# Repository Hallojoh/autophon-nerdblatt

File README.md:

We try to get an flipboard display running on a new PCB

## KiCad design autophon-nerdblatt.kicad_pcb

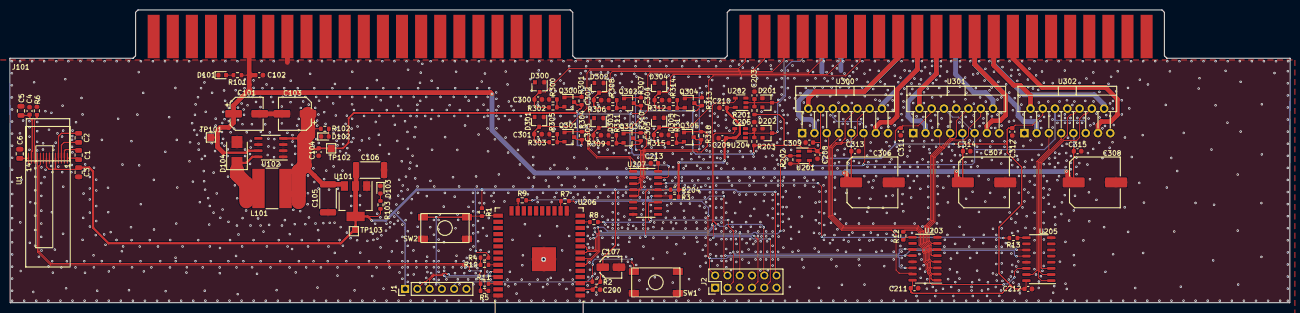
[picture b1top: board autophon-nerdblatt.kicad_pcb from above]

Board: 2 copper layers, 265.0 x 60.6 mm, 115 parts (0 on the bottom side), 82 nets.

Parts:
C1, C2, C3: 1u; C_0805_2012Metric
C4, C104, C200, C300, C301, C302, C303, C304, C305, C309, C311, C312: 100n; C_0603_1608Metric
C5, C6: 10u; C_0805_2012Metric
C101, C103: 120u; CP_Elec_6.3x7.7
C102, C313, C314, C315: 100n/25V; C_0603_1608Metric
C105, C106: 10u; C_2512_6332Metric
C107: 22u; C_Elec_4x5.8
C203, C205, C208, C209, C210: 1n; C_0603_1608Metric
C211, C212, C213: 10n; C_0603_1608Metric
C306, C307, C308: 470uF; C_Elec_10x10.2
D101, D102, D103: LED gn; LED_0603_1608Metric
D104: MBRS130; D_SMB
D201, D202, D300, D301, D302, D303, D304, D305: 5v6; D_SOT-23_ANK
J1: Conn_01x06_Female; PinHeader_1x06_P2.54mm_Vertical
J2: Conn_02x06_Odd_Even; PinHeader_2x06_P2.54mm_Vertical
J101: board-edge-connector; autophon-pcb-edge-connector
L101: 100uH; L_Bourns-SRN8040_8x8.15mm
Q300, Q301, Q302, Q303, Q304, Q305: BSS84; SOT-23
R1, R2, R3, R4, R5, R202, R204, R301, R302, R304, R305, R307, R308, R310, R311, R313, R314, R316, R317: 10k; R_0603_1608Metric
R6: 910k; R_0603_1608Metric
R7, R8, R9, R10, R11, R12, R13: 33R; R_0603_1608Metric
R101: 1k2; R_0603_1608Metric
R102: 200R; R_0603_1608Metric
R103: 100R; R_0603_1608Metric
R201, R203: 4k7; R_0603_1608Metric
R300, R303, R306, R309, R312, R315: 51R; R_0603_1608Metric
SW1, SW2: SW_Push; NAMAE_JTP-1138
TP101: 24V; TestPoint_Pad_1.5x1.5mm
TP102: 5V; TestPoint_Pad_1.5x1.5mm
TP103: VCC; TestPoint_Pad_1.5x1.5mm
U1: EA_W096016-XALW; EA W096016-XA
U101: LM1117-3.3; SOT-223-3_TabPin2
U102: LM2594M-5.0; SO-8_3.9x4.9mm_P1.27mm
U201, U202, U204: SN74LV1T34; SOT-23-5
U203, U205, U207: 74AHCT595; SO-16_3.9x9.9mm_P1.27mm
U206: ESP32-WROOM-32
U300, U301, U302: L298HN; TO-220-15_P2.54x2.54mm_StaggerOdd_Lead4.58mm_Vertical

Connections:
+5V: C103.1, C104.1, C105.1, C208.1, C211.1, C212.1, C213.1, C309.1, C311.1, C312.1, L101.2, Q300.3 (D), Q301.3 (D), Q302.3 (D), Q303.3 (D), Q304.3 (D), Q305.3 (D), R102.1, R201.1, R203.1, R301.1, R304.1, R307.1, R310.1, R313.1, R316.1, TP102.1, U101.3 (VI), U102.4 (FB), U201.5 (VCC), U203.16 (VCC), U205.16 (VCC), U207.16 (VCC), U300.4 (Vs), U301.4 (Vs), U302.4 (Vs)
+24V: C101.1, C102.1, C306.1, C307.1, C308.1, C313.1, C314.1, C315.1, J101.6A, J101.39B, R101.1, TP101.1, U102.7 (VIN), U300.9 (Vss), U301.9 (Vss), U302.9 (Vss)
/ESP32_Shiftregs/ESP32_EN: J1.5, R2.2, SW1.2, U206.3 (EN)
/ESP32_Shiftregs/ESP32_GPIO0: J1.4, R1.2, SW2.2, U206.25 (IO0)
/ESP32_Shiftregs/ESP32_RX: J1.2, U206.34 (RXD0/IO3)
/ESP32_Shiftregs/ESP32_TX: J1.3, U206.35 (TXD0/IO1)
/ESP32_Shiftregs/HALL_INDEX_3V: J2.9, U202.4 (Y), U206.7 (IO35)
/ESP32_Shiftregs/HALL_ROTOR_3V: J2.10, U204.4 (Y), U206.6 (IO34)
/ESP32_Shiftregs/I2C_SCL: R11.1, U206.36 (IO22)
/ESP32_Shiftregs/I2C_SDA: R10.1, U206.33 (IO21)
/ESP32_Shiftregs/MOT_EN_3V: J2.6, R202.1, U201.2 (A), U206.8 (IO32)
/ESP32_Shiftregs/SER_QH_2: R13.2, U207.14 (SER)
/ESP32_Shiftregs/SPI_CLK: R8.1, U206.13 (IO14)
/ESP32_Shiftregs/SPI_CLK-t: J2.3, R8.2, U203.11 (SRCLK), U205.11 (SRCLK), U207.11 (SRCLK)
/ESP32_Shiftregs/SPI_COPI: R7.1, U206.16 (IO13)
/ESP32_Shiftregs/SPI_COPI-t: J2.2, R7.2, U203.14 (SER)
/ESP32_Shiftregs/~HALL_EN_3V~: J2.7, R204.2, U206.9 (IO33), U207.13 (~OE)
/ESP32_Shiftregs/~SPI_CSO-t~: J2.4, R3.2, R9.2, U203.12 (RCLK), U205.12 (RCLK), U207.12 (RCLK)
/ESP32_Shiftregs/~SPI_CSO~: R9.1, U206.23 (IO15)
ABCDEF_HALL_GND: C3.2, C4.2, C5.2, C6.2, C101.2, C102.2, C103.2, C104.2, C105.2, C106.2, C107.2, C200.2, C203.2, C205.2, C208.2, C209.2, C210.2, C211.2, C212.2, C213.2, C300.2, C301.2, C302.2, C303.2, C304.2, C305.2, C306.2, C307.2, C308.2, C309.2, C311.2, C312.2, C313.2, C314.2, C315.2, D101.1 (K), D102.1 (K), D103.1 (K), D104.2 (A), D201.2 (A), D202.2 (A), D300.2 (A), D301.2 (A), D302.2 (A), D303.2 (A), D304.2 (A), D305.2 (A), J1.6, J2.1, J2.5, J2.8, J2.11, J101.8A, J101.17B, J101.18B, J101.37B, R6.1, R202.2, R302.2, R305.2, R308.2, R311.2, R314.2, R317.2, SW1.1, SW2.1, U1.7 (VSS), U101.1 (GND), U102.1 (NC), U102.2 (NC), U102.3 (NC), U102.6 (GND), U201.3 (GND), U202.3 (GND), U203.8 (GND), U203.13 (~OE), U204.3 (GND), U205.8 (GND), U205.13 (~OE), U206.1 (GND), U206.15 (GND), U206.38 (GND), U206.39 (GND), U207.8 (GND), U300.1 (SENSE_A), U300.8 (GND), U300.15 (SENSE_B), U301.1 (SENSE_A), U301.8 (GND), U301.15 (SENSE_B), U302.1 (SENSE_A), U302.8 (GND), U302.15 (SENSE_B)
ABCDEF_HALL_INDEX: C203.1, D201.1 (K), J101.20B, R201.2, U202.2 (A)
ABCDEF_HALL_ROTOR: C205.1, D202.1 (K), J101.19B, R203.2, U204.2 (A)
A_HALL_PWR: C300.1, D300.1 (K), J101.23A, R300.1
A_MOT_NEG: J101.14B, U300.3 (OUT2)
A_MOT_NEG_DRV: U203.1 (QB), U300.7 (IN2)
A_MOT_POS: J101.31A, U300.2 (OUT1)
A_MOT_POS_DRV: U203.15 (QA), U300.5 (IN1)
B_HALL_PWR: C301.1, D301.1 (K), J101.24A, R303.1
B_MOT_NEG: J101.13B, U300.14 (OUT4)
B_MOT_NEG_DRV: U203.3 (QD), U300.12 (IN4)
B_MOT_POS: J101.32A, U300.13 (OUT3)
B_MOT_POS_DRV: U203.2 (QC), U300.10 (IN3)
C_HALL_PWR: C302.1, D302.1 (K), J101.25A, R306.1
C_MOT_NEG: J101.12B, U301.3 (OUT2)
C_MOT_NEG_DRV: U203.5 (QF), U301.7 (IN2)
C_MOT_POS: J101.33A, U301.2 (OUT1)
C_MOT_POS_DRV: U203.4 (QE), U301.5 (IN1)
D_HALL_PWR: C303.1, D303.1 (K), J101.27A, R309.1
D_MOT_NEG: J101.11B, U301.14 (OUT4)
D_MOT_NEG_DRV: U203.7 (QH), U301.12 (IN4)
D_MOT_POS: J101.35A, U301.13 (OUT3)
D_MOT_POS_DRV: U203.6 (QG), U301.10 (IN3)
E_HALL_PWR: C304.1, D304.1 (K), J101.28A, R312.1
E_MOT_NEG: J101.10B, U302.3 (OUT2)
E_MOT_NEG_DRV: U205.1 (QB), U302.7 (IN2)
E_MOT_POS: J101.36A, U302.2 (OUT1)
E_MOT_POS_DRV: U205.15 (QA), U302.5 (IN1)
F_HALL_PWR: C305.1, D305.1 (K), J101.29A, R315.1
F_MOT_NEG: J101.9B, U302.14 (OUT4)
F_MOT_NEG_DRV: U205.3 (QD), U302.12 (IN4)
F_MOT_POS: J101.37A, U302.13 (OUT3)
F_MOT_POS_DRV: U205.2 (QC), U302.10 (IN3)
GLOBAL_MOT_EN: U201.4 (Y), U300.6 (EnA), U300.11 (EnB), U301.6 (EnA), U301.11 (EnB), U302.6 (EnA), U302.11 (EnB)
I2C_SCL-t: R5.2, R11.2
I2C_SDA-t: R4.2, R10.2
unnamed: C1.1, U1.1 (C2N)
unnamed: C1.2, U1.2 (C2P)
unnamed: C2.1, U1.3 (C1P)
unnamed: C2.2, U1.4 (C1N)
unnamed: C4.1, C5.1, U1.13 (VCOMH)
unnamed: C6.1, U1.14 (VCC)
unnamed: D101.2 (A), R101.2
unnamed: D102.2 (A), R102.2
unnamed: D103.2 (A), R103.2
unnamed: D104.1 (K), L101.1, U102.8 (OUT)
unnamed: Q300.2 (S), R300.2, R302.1
unnamed: Q301.2 (S), R303.2, R305.1
unnamed: Q302.2 (S), R306.2, R308.1
unnamed: Q303.2 (S), R309.2, R311.1
unnamed: Q304.2 (S), R312.2, R314.1
unnamed: Q305.2 (S), R315.2, R317.1
unnamed: R6.2, U1.12 (IREF)
unnamed: R12.1, U203.9 (QH')
unnamed: R12.2, U205.14 (SER)
unnamed: R13.1, U205.9 (QH')
VCC: C3.1, C106.1, C107.1, C200.1, C209.1, C210.1, J1.1, J2.12, R1.1, R2.1, R3.1, R4.1, R5.1, R103.1, R204.1, TP103.1, U1.5 (VBAT), U1.8 (VDD), U101.2 (VO), U202.5 (VCC), U204.5 (VCC), U206.2 (VDD)
~A_HALL_PWR_EN~: Q300.1 (G), R301.2, U207.15 (QA)
~B_HALL_PWR_EN~: Q301.1 (G), R304.2, U207.1 (QB)
~C_HALL_PWR_EN~: Q302.1 (G), R307.2, U207.2 (QC)
~D_HALL_PWR_EN~: Q303.1 (G), R310.2, U207.3 (QD)
~E_HALL_PWR_EN~: Q304.1 (G), R313.2, U207.4 (QE)
~F_HALL_PWR_EN~: Q305.1 (G), R316.2, U207.5 (QF)

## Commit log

2020-08-08 Create README.md
    Created a README to be modified.
2020-12-04 Added footprints.
2020-12-06 caps for long high impedance traces. distributor info.
2020-12-06 New Footprint for L
2020-12-06 not putting .zipfiles into the repo
2020-12-12 more C vor Logic and placing first groups of parts
2020-12-12 first traces
2020-12-12 GND-Plane on endge connector and BOT
2020-12-12 esp32-spi: changed labels, C removed, esp32 programming
    * Added esp32 programming connector + buttons for reset, gpio0
    * Removed C on local signals (between to chips on board)
    (3.3v between ESP and voltage translators)
    * changed some labels from globals to local labels on sheet
2020-12-12 Removing a few more unnecessary 1nF.
2020-12-12 removed old FF.pro abandoned project file
2020-12-13 all traces routed. ready for cleanup
2020-12-14 Main schematic, unuglify main power.
    +24V trace was crossing the main board connector which made
    it almost impossible to select with kicad tools.
2020-12-14 esp32_shiftregs: add comments and labels to esp32 pins
    Additional remarks for pin use, pullup on ~CS0 (also
    relevant during boot of esp32)
2020-12-14 esp32/shiftreg: add connector for ext. controller
2020-12-14 Add external connector, and swapped ESP pins.
    Pins for motor enable, hallsensor enable and
    readback of hall-sensors have been moved to
    more appropriate pins.
    (2 to input only, and the enable pins to
    gpios with no interesting auxiliary functions)
2020-12-14 collateral damage from running the annotate function
2020-12-19 Zener diodes now 5v6
2020-12-20 add Display sheet and I2C Pullups
2020-12-20 Display Routing
2020-12-24 Layout cleanup
2020-12-25 GND Vias and Bus Resistors in series.
2020-12-25 Logo, fun and cleanup
